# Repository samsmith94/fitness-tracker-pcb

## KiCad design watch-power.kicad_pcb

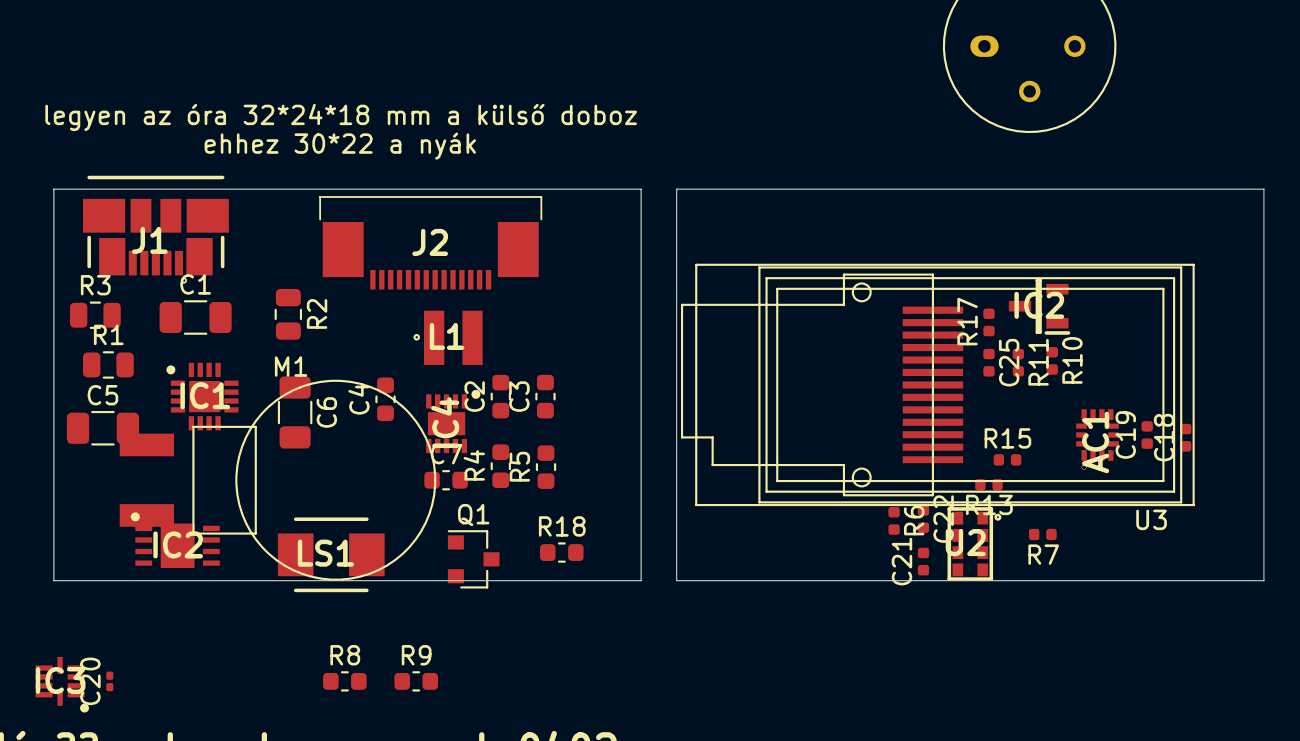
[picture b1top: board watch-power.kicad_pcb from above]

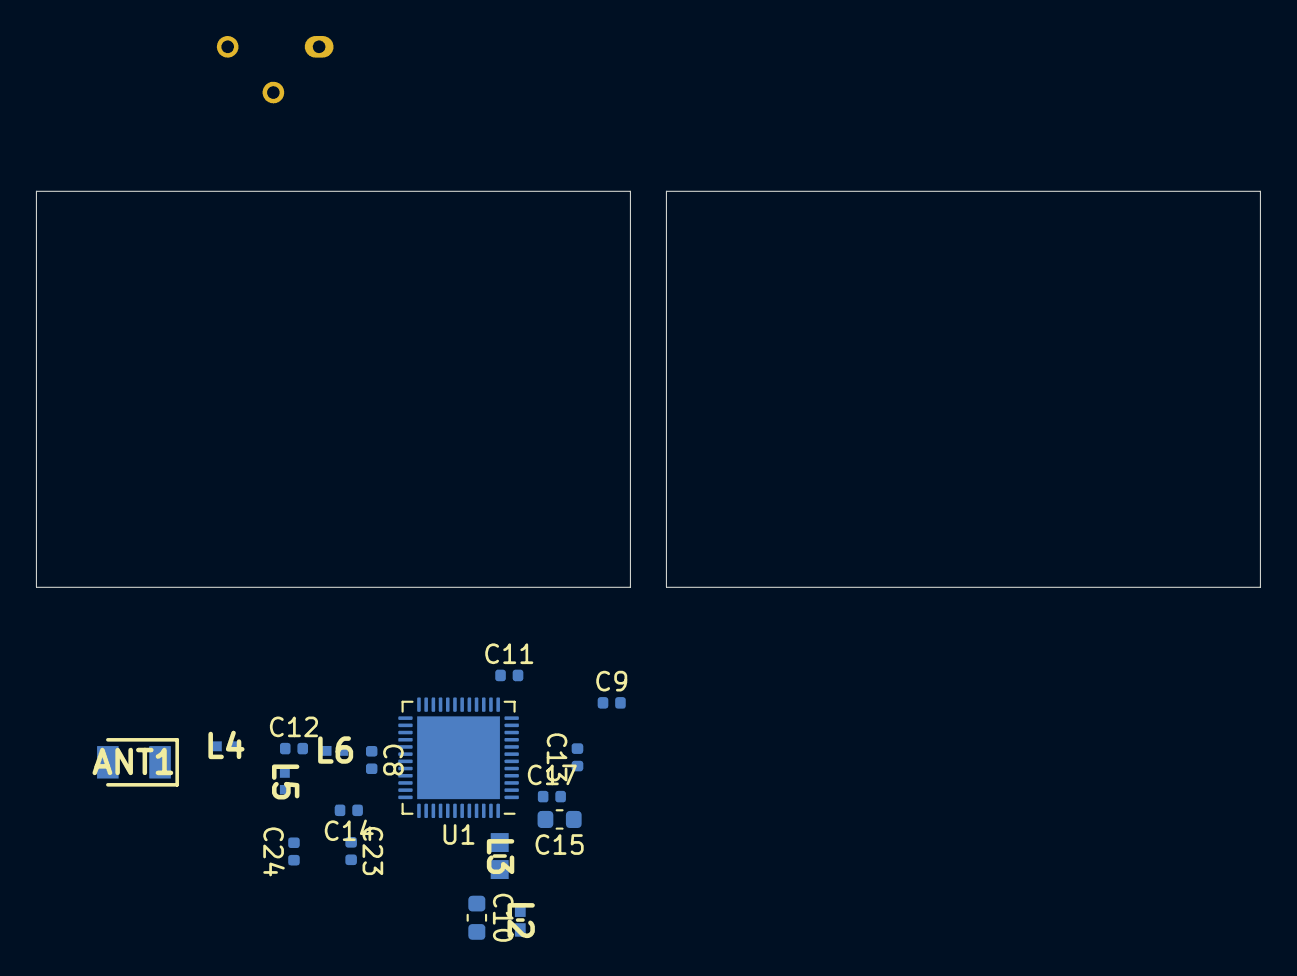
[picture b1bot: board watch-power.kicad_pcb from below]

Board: 2 copper layers, 68.0 x 22.0 mm, 61 parts (18 on the bottom side), 32 nets, no tracks yet.

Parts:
AC1: LSM6DSOXTR; LGA-14_1
ANT1: 2450AT18B100E; ANTC3216X140N
C1: 1uF; C_1206_3216Metric
C2, C3, C4: 10uF; C_0603_1608Metric
C5, C6: 4.7uF; C_1206_3216Metric
C7: 0.1uF; C_0603_1608Metric
C8: 0.8pF; C_0402_1005Metric
C9, C13, C23, C24: 12pF; C_0402_1005Metric
C10: 1.0uF; C_0603_1608Metric
C11, C17, C18, C19, C25: 100nF; C_0402_1005Metric
C12: 2.7pF; C_0402_1005Metric
C14: 100pF; C_0402_1005Metric
C15: 4.7uF; C_0603_1608Metric
C20: 0.1uF; C_0201_0603Metric
C21, C22: 1uF; C_0402_1005Metric
IC1: BQ24230; QFN50P300X300X100-17N-D
IC2: MMBT2222ALT1G; SOT96P237X111-3N
IC2#2: LC709203FQH-01TWG; SON65P400X300X80-9N
IC3: DRV2603RUNR; QFN50P200X200X80-10N-D
IC4: TPS63030; SON50P250X250X80-11N-D
J1: 47346-0001
J2: 1-1734592-4; 117345924
L1: LPS3015-103MRB; LPS3015
L2: HK100515NJ-T; INDC1005X55N
L3: LBMF1608T100K; INDC1608X100N
L4: LQP15MN1N8B02D; LQP15MN10NG02D
L5: LQP15MN2N7B02D; LQP15MN10NG02D
L6: LQP15MN3N9B02D; LQP15MN10NG02D
LS1: CMT-4023S-SMT-TR; CMT-4023S
M1: Vibramotor
Q1: BC847; SOT-23
Q1#2: 2N2219; TO-39-3
R1, R2, R3: R; R_0805_2012Metric
R4, R5: R; R_0603_1608Metric
R6: 22R; R_0402_1005Metric
R7, R11, R13, R15: 10k; R_0402_1005Metric
R8, R9: 100k; R_0603_1608Metric
R10: 1k; R_0402_1005Metric
R17: 100R; R_0402_1005Metric
R18: 1k; R_0603_1608Metric
U1: nRF52832-QFxx; QFN-48-1EP_6x6mm_P0.4mm_EP4.6x4.6mm
U2: APDS9960; APDS-9950
U3: ST7735; ST7735_curved

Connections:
+3V3: AC1.2, AC1.3, AC1.5, AC1.8, C4.1, C6.1, C18.1, C19.1, C20.1, C21.1, C25.1, LS1.1, R6.2, R7.1, R8.2, R9.2, R11.1, R13.1, R15.1, U2.5, U3.10, U3.12
ANT: C8.1, L6.1, U1.30
BATT_M: AC1.6, AC1.7, C1.2, C3.2, C4.2, C5.2, C6.2, C7.2, C8.2, C9.2, C10.2, C11.2, C13.2, C14.2, C15.2, C17.2, C18.2, C19.2, C20.2, C21.2, C22.2, C23.2, C24.2, C25.2, IC2.2, J1.5, L5.1, Q1.2, R1.1, R3.1, R5.2, U1.31, U1.45, U1.49, U2.6, U3.8, U3.13
DCDC: L3.2, U1.47
DEC1: C17.1, U1.1
DEC3: C14.1, U1.33
DEC4: C10.1, L2.1, U1.46
DISPLAY_BACKLIGHT: R10.2, R11.2
GESTURE_INT: R7.2, U2.2
GESTURE_SCL: R13.2, U2.7
GESTURE_SDA: R15.2, U2.1
unnamed: ANT1.1, L4.2
unnamed: C1.1, J1.1
unnamed: C3.1, R4.1
unnamed: C12.1, L4.1, L5.2
unnamed: C12.2, L6.2
unnamed: C22.1, R6.1, U2.8
unnamed: IC1.2, L1.2
unnamed: IC1.4, L1.1
unnamed: IC1.10, R4.2, R5.1
unnamed: IC2.1, IC2#2.1, R10.1
unnamed: IC2.3, IC2#2.3, R17.2
unnamed: L2.2, L3.1
unnamed: LS1.2, Q1.3
unnamed: Q1.1, Q1#2.1, R18.1
unnamed: R17.1, U3.11
unnamed: U2.3, U2.4
VDD_nRF: C11.1, C15.1, U1.13, U1.36, U1.48
XC1: C24.1, U1.34
XC2: C23.1, U1.35
XL1: C13.1, U1.2
XL2: C9.1, U1.3

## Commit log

2020-09-12 init
2020-09-12 add some schematic parts around nrf52
2020-09-26 big save
2020-09-30 save
2020-10-01 add piezo
2020-12-11 save before drastic rearranger
